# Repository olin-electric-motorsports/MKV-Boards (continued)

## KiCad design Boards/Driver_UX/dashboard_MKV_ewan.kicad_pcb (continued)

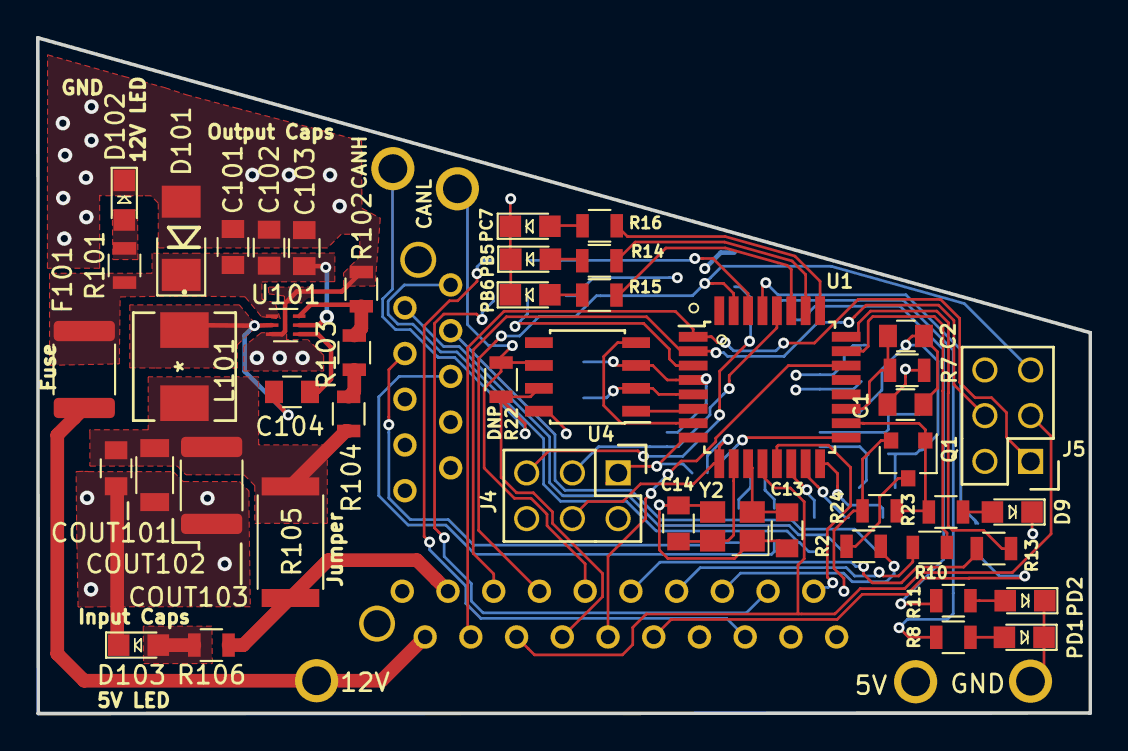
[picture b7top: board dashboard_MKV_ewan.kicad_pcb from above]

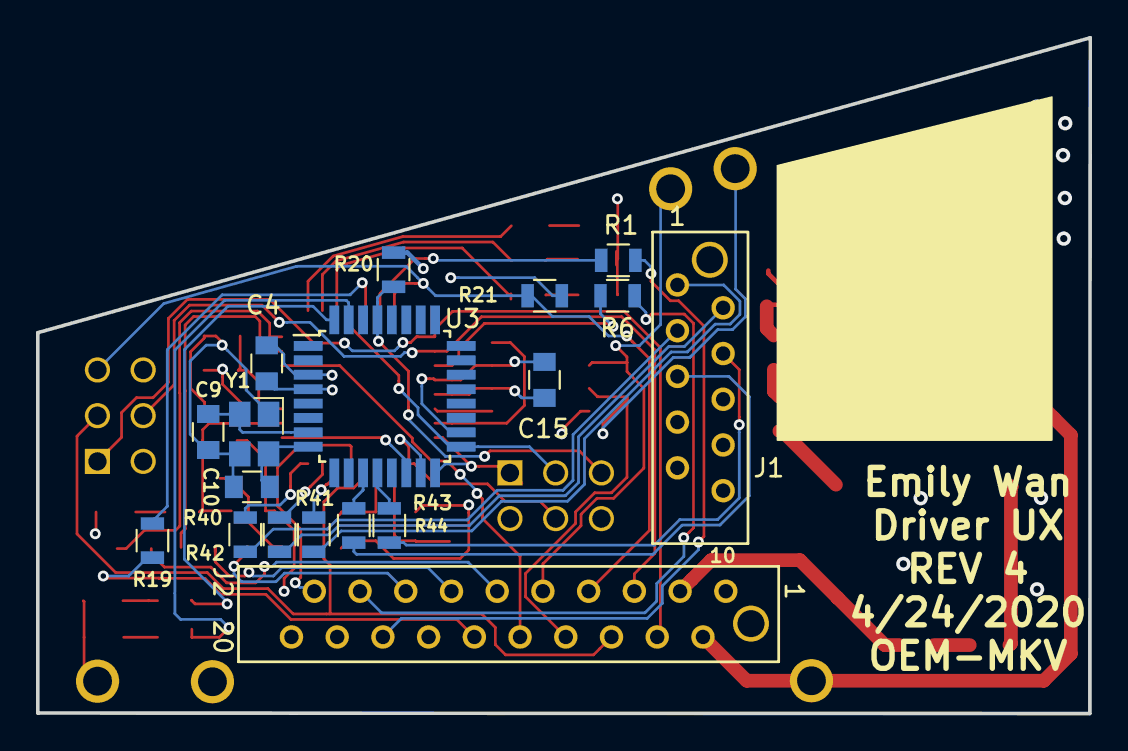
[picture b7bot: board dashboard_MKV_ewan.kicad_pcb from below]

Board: 4 copper layers, 58.5 x 37.5 mm, 70 parts (18 on the bottom side), 65 nets.

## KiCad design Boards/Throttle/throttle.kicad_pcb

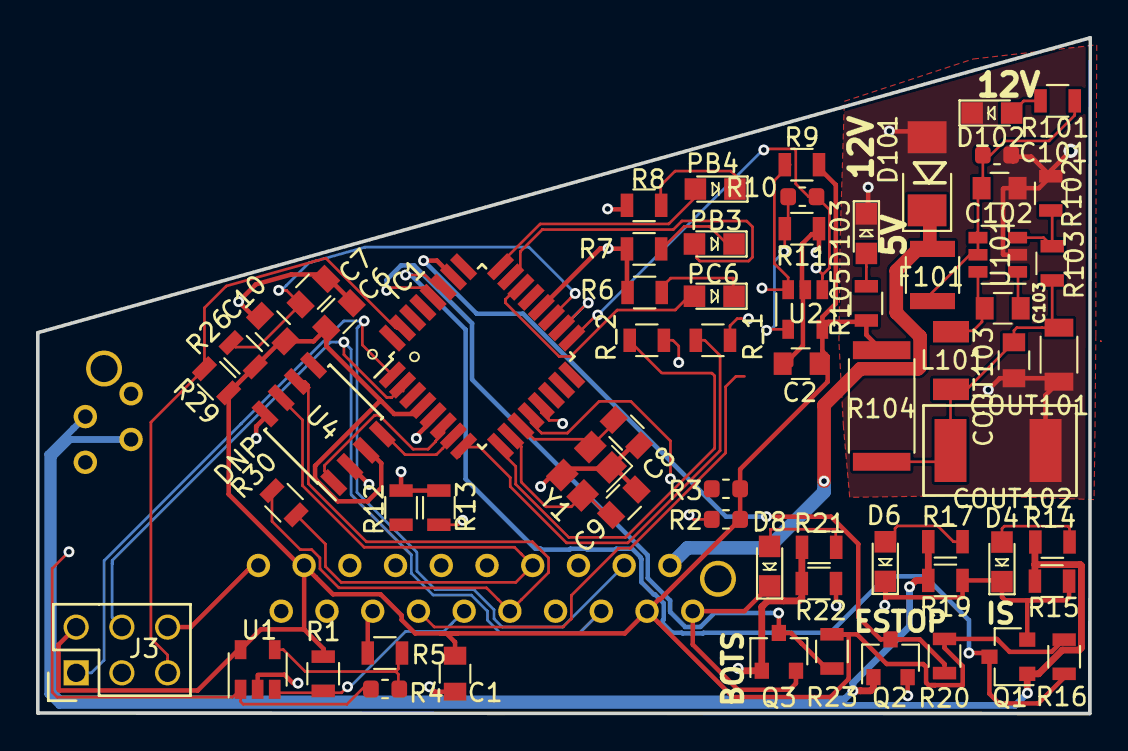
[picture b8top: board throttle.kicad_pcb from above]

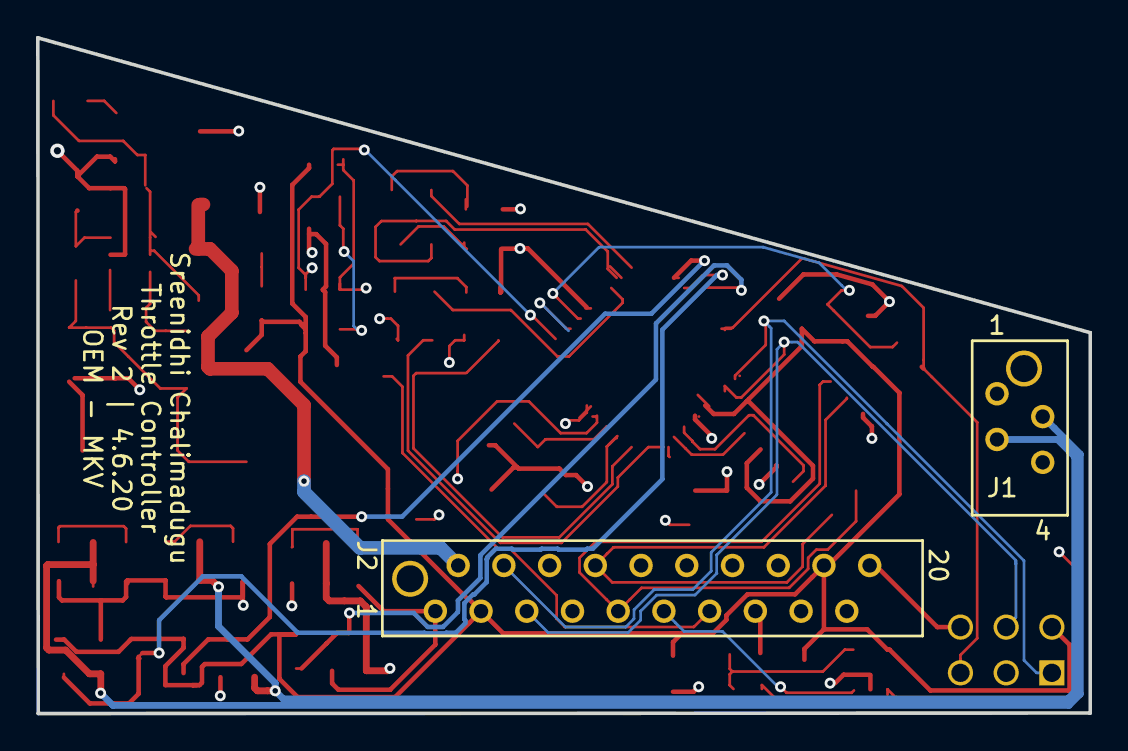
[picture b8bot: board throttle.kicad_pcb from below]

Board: 4 copper layers, 58.5 x 37.5 mm, 68 parts (2 on the bottom side), 49 nets.

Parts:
C1, C2, C6, C10, C103: C_0.1uF; C_0805_OEM
C7: C_100pF; C_0805_OEM
C8, C9: C_30pF; C_0805_OEM
C101: C_0.1uF; C_0603_1608Metric
C102: C_2.2uF; C_0805_OEM
COUT101: C_22uF; C_1206_OEM
COUT102: C_33uF; Fuse_1812
COUT103: C_47uF; C_0805_OEM
D4, D6, D8, D102, D103: LED_0805; LED_0805_OEM
D101: D_Zener_18V; DO-214AA
F101: F_500mA_16V; Fuse_1210
IC1: ATMEGA16M1; TQFP-32_7x7mm_Pitch0.8mm
J1: micromatch_female_TOP_ENTRY_locking_4; micromatch_female_vert_4
J2: micromatch_female_TOP_ENTRY_locking_20; micromatch_female_vert_20
J3: CONN_02X03; Pin_Header_Straight_2x03
L101: L_100uH
PB3, PB4: LED_0805; LED_0805_OEM
PC6: LED_0805; LED_0805_OEM
Q1, Q2, Q3: SSM3K333R; SOT-23F
R1, R9: R_1M; R_0805_OEM
R2, R3: R_0; R_0603_1608Metric
R4, R10: R_0-formula; R_0603_1608Metric
R5, R11: R_2.2k; R_0805_OEM
R6, R7, R8, R101, R105: R_200; R_0805_OEM
R12, R13: R_22K; R_0805_OEM
R14, R17, R21: R_1k; R_0805_OEM
R15, R19, R22: R_100k; R_0805_OEM
R16, R20, R23, R29: R_10k; R_0805_OEM
R26: R_100; R_0805_OEM
R30: R_120 DNP; R_0805_OEM
R102: R_25K; R_0805_OEM
R103: R_100K; R_0805_OEM
R104: R_0_2512; R_2512_OEM
R_1, R_2: R_200; R_0805_OEM
U1, U2: MCP6001; SOT-23-5_OEM
U4: CAN_Transceiver; SOIC-8_3.9x4.9mm_Pitch1.27mm_OEM
U101: TPS560430YF; SOT-23-6_OEM
Y1: Crystal_SMD; Crystal_SMD_FA238

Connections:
+12V: D101.1, F101.2, J2.2
/CANH: J2.8, R30.1, U4.7
/CANL: J2.9, R30.2, U4.6
/DRIVE_MODE_SENSE: IC1.13, J2.19, R13.1
/LED1: J2.16, R_1.1
/LED2: J2.17, R_2.1
/MISO: IC1.1, J2.4, J3.1
/MOSI: IC1.2, J2.5, J3.4
/PROGRAMMINGLED1: IC1.22, PC6.2
/PROGRAMMINGLED2: IC1.23, PB3.2
/PROGRAMMINGLED3: IC1.24, PB4.2
/RESET: IC1.31, J2.7, J3.5, R29.2
/RXCAN: IC1.7, U4.4
/SCK: IC1.12, J2.6, J3.3
/SS_BOTS: J1.1, Q3.1, R21.1, R22.1
/SS_BOTS_OUT: IC1.28, Q3.3, R23.2
/SS_COCKPIT_ESTOP: J1.3, Q2.1, R17.1, R19.1
/SS_ESTOP_OUT: IC1.26, Q2.3, R20.2
/SS_INERTIA_OUT: IC1.27, Q1.3, R16.2
/SS_INERTIA_SWITCH: J1.2, Q1.1, R14.1, R15.1
/THROTTLE1SENSING: IC1.17, R10.1, U2.1
/THROTTLE1_RIGHT_SENSE: J2.11, R1.2, U1.3
/THROTTLE2SENSING: IC1.18, R4.1, U1.1
/THROTTLE2_LEFT_SENSE: J2.14, R9.2, U2.3
/TXCAN: IC1.6, U4.1
GND: C1.1, C2.1, C6.2, C7.2, C8.2, C9.2, C10.2, C101.2, C102.2, COUT101.2, COUT102.2, COUT103.2, D4.1, D6.1, D8.1, D101.2, D102.1, D103.1, IC1.5, IC1.20, J1.4, J2.1, J2.12, J2.15, J2.20, J3.6, Q1.2, Q2.2, Q3.2, R5.2, R6.2, R7.2, R8.2, R11.2, R12.1, R13.2, R15.2, R19.2, R22.2, R102.2, U1.2, U2.2, U4.2, U4.8, U101.2, Y1.2, Y1.4
unnamed: C7.1, IC1.19, R26.2
unnamed: C8.1, IC1.11, Y1.1
unnamed: C9.1, IC1.10, Y1.3
unnamed: C101.1, C102.1, F101.1, R101.1, U101.4, U101.5
unnamed: C103.1, L101.1, U101.6
unnamed: C103.2, U101.1
unnamed: COUT101.1, COUT102.1, COUT103.1, L101.2, R103.1, R104.1
unnamed: PC6.1, R6.1
unnamed: PB3.1, R7.1
unnamed: PB4.1, R8.1
unnamed: D4.2, R14.2
unnamed: D6.2, R17.2
unnamed: D8.2, R21.2
unnamed: D102.2, R101.2
unnamed: D103.2, R105.2
unnamed: IC1.8, R_1.2
unnamed: IC1.9, R_2.2
unnamed: J2.10, R2.1
unnamed: J2.13, R3.2
unnamed: R4.2, R5.1, U1.4
unnamed: R10.2, R11.1, U2.4
unnamed: R102.1, R103.2, U101.3
VCC: C1.2, C2.2, C6.1, C10.1, IC1.4, J2.3, J2.18, J3.2, R1.1, R2.2, R3.1, R9.1, R16.1, R20.1, R23.1, R26.1, R29.1, R104.2, R105.1, U1.5, U2.5, U4.3

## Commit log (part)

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2019-12-02 adding fuses for balancing circuitry
2019-12-02 MegaBoard connectors and dxf
2019-12-02 Finished Schematic with Adi's comments, created V1.0 of Layout
2019-12-03 Debugging board
2019-12-03 Finalize the Suspension Travel Layout
    Move a sensing label to the proper pin on the microcontroller
2019-12-03 BSPD Rev 1 finished
2019-12-03 Generate BSPD/brakelight gerbers
2019-12-03 Reordered shutdown senses on pcb
2019-12-03 Rev. 1
2019-12-03 Finished first(third) pass of schematic
2019-12-03 minor schematic fixes, began layout
2019-12-03 Finish rough draft of schematic
2019-12-03 schematic v2.0 was finally finished
2019-12-03 update template to 1K resistor for 12V led
2019-12-04 fixed bucl resistor mistake
2019-12-04 Add LEDs to shutdown sense board
    Still need to figure out if we need a shutdown sense circuit for Main Fuse
    or if it will come over CAN.
    * Renamed "Brakelight_BSPD" to "BSPD_Brakelight" to stick with naming
    conventions.
2019-12-05 Adds traces to SS board
    No buck convertor or VCC lines in this commit. Still need to
    figure out what is happening with the Main Fuse (i.e. whether
    or not the sense circuit will be on this board or elsewhere).
2019-12-05 Add final traces before importing buck
2019-12-05 laid out components without wires
2019-12-06 Layout V2.0
2019-12-06 Layout V2.5, moved capcaitors closer to chips, eliminates vias in sck, chenaged buck converter positioning after Adi's checkin
2019-12-06 began work on custom bms schematic
2019-12-06 Schematic checked off and PCB Begun
2019-12-06 Complete shutdown sense schematic with buck converter
2019-12-06 Replace 1k with 200k for 5V LEDs
    * Rotate ATmega to be horizontal (allows for fewer route turns)
    * Make LSD driver lines same as VCC (10 mils)
2019-12-10 Edit Schematics
2019-12-10 IMD push
2019-12-10 layout almost complete
2019-12-10 only missing vcc traces now
2019-12-12 Adding First Pass of High Current Buck (3A max)
2019-12-13 Final tweaks
2019-12-13 updates for checkoff
2019-12-13 lcd board with new buck
2019-12-13 Generate BOM and Gerber files
2019-12-13 Final Schamtic and Layout
2019-12-13 Sterring 1st passed layout
2019-12-14 DUX layout Rev1.2
2019-12-15 Charging Cart LCD PCB Layout & Schematic
2019-12-16 Finish schematic
2019-12-16 first pass layout with new buck.
2019-12-17 Beginning changes for laying out board.
2019-12-18 Add draft for lucky to review
2019-12-19 Add small changes
2019-12-20 Add in DXF and start incorporating Lucky's feedback
2019-12-21 Add most revisions besides strain gauge circuits
2019-12-21 Add draft that organizes non-strain gauge circuit parts
2019-12-23 Modify Charging LCD Layout
2019-12-23 Modified buck for throttle board
2019-12-23 Add strain gauge circuits into board cutting boundary
2019-12-23 Improve organization
2019-12-24 Fixed Buck for LCD Screen
2019-12-26 Start wiring strain gauge subcircuits to mux
2019-12-26 Make some improvements to trace organization
2019-12-26 Rotate MUX to optimize its corresponding traces
2019-12-26 Make F.SilkS layer legible
2019-12-28 Minimmize bottom layer traces
2019-12-28 Add logo and name
2019-12-28 Remove vestigial files
2019-12-28 Add gerbers folder and its zip
2019-12-28 added BOM for Chassis_Strain
2019-12-30 deleted extra files
2020-01-02 new edits to layout
2020-01-03 Inital Setup
2020-01-03 Completed LV Interface Rev 1 Things that need to be addressed: - 12V plane is cut off near Ampseal 35 - BSPD CAN Lines are not standard (would be easy to fix on both ends I think) - Could only reason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
    Other changes that were made
    - Significant ampseal changes to accomodate Cooling Board Changes
    - All changes are reflected in Board Interface Sheet
2020-01-03 Saving
2020-01-04 Fixing Charging Cart Dependencies
2020-01-04 Fixed IMD Latch Schematic + Finished Layout
2020-01-04 Fixed VCC & CAN Traces. Added Name Silkscreen
2020-01-04 added new dxf for comparison
2020-01-04 Update micromatch with new pin outs
    Moved TXCAN and RXCAN to positions 3 and 4 to match the LV
    Interface board
2020-01-05 new edits: crystal, retrace
2020-01-05 final lcd screen board
2020-01-05 final final lcd board - added silk screen.
2020-01-05 layout ready for first review
2020-01-06 layout updates (1/5 @20:25)
2020-01-06 layout with graphics
2020-01-06 final layout changes
2020-01-07 gerb files
2020-01-07 pcb commit
2020-01-09 second rev of board
2020-01-11 New DXF stretched out
2020-01-13 fixed footprint error and file cleanup
2020-01-13 acc interface schematic donee
2020-01-15 started internal acc interface
2020-01-15 Save
2020-01-17 Begin Layout
2020-01-17 Revert "Begin Layout"
    This reverts commit f66e97611986f6cb10e89dffa2fa205961dd2a3d.
2020-01-18 Updating AIR Plus Models
2020-01-22 first pass of acc interface and rev1.1 of periph layout
2020-01-23 Edit Layout
2020-01-24 Update BOMs (just to be safe)
2020-01-24 created BOM for board
2020-01-24 BOM for LCD Screen
2020-01-24 rearranged components without traces
2020-01-24 made changes to coding pins, saving before turning other pin
2020-01-24 Necessary tweaks to Charging Cart LCD PCB
2020-01-24 Add BOM
2020-01-25 Air Minus updates 1.24.20 (for Corey)
2020-01-25 Turned pins around and fixed board. Finished Rev 2.
2020-01-25 Turned pins for repositioning. Finished Rev 2
2020-01-26 Board finished, pushing Rev 2
2020-01-26 Adding 3d models of lv Interface, Brakelight, BSPD and Shutdown Boards
2020-01-27 Adding GLVMS to the shutdown circuit
2020-01-27 Layout updated to include GLVMS in Shutdown Circuit
2020-01-27 New connector layouts for air +
2020-01-27 more 3d models
2020-01-28 Fixing Microcmatch 3d models
2020-01-28 Removing Random Text
2020-01-28 HV traces updated
2020-01-28 Rev 3, reduced number of vias and was able to reorganize some tracks
2020-01-29 Controller flipped to back of board
2020-01-30 create bom
2020-01-31 Second Rev PCB
2020-01-31 Fixed labels
2020-02-01 Remove unnecessary files
2020-02-01 Add PDFs of Rev 1 schematics/layouts
2020-02-01 Updating DXF
2020-02-01 shrinking pcb complete
2020-02-01 Minor fixes
2020-02-01 Removed on board cooling Fusing and added additional battery lines
2020-02-02 fixed design rules for via
2020-02-03 added silks to AIR mount plus + gerbs
2020-02-03 made changes to LV BMS board
2020-02-04 Adding cutout notches
2020-02-04 imported new dxf, need to finish drawing sense lines from mm and moving LEDs
2020-02-04 Finished Super Early draft of LV BMS board
2020-02-05 Completed BSPD rev 2
2020-02-05 Addressing review comments ahead of meeting
2020-02-05 Adding Testing Points, Moved Zener Diode (Corrected Orientation)
2020-02-06 Update buck and add test points
    Also remove SCK line from under the ATMega, moved it
    to prevent noise.
2020-02-06 Updated buck on BSPD and added test points
2020-02-07 minor TSAL updates
2020-02-07 Adding lvinterface gerbers
2020-02-07 tons of changes, bug fixes, errors with screw terminals
2020-02-08 Added bypass cap to Logic block; new core layout for ss layout
2020-02-09 modded sch for better routing | layout v1
2020-02-09 new transformer, mounting hole, moved I sensor
2020-02-09 fixed adis suggested changes
2020-02-11 fixed folder problem
2020-02-11 lots of changes to improve naming conventions, consolidate circuitry
2020-02-11 updated final rev 2 with labels and test points
2020-02-12 New BMS core DXF, proper GLV HV spacing
2020-02-13 Final, and slight, changes to layout
2020-02-13 BMS core rev1.0 for shipment
2020-02-13 Updating Gates Names
2020-02-14 added in resistor values
2020-02-14 added mounting holes
2020-02-14 started changes to TSAL schematic
2020-02-15 documented a ton of junk
2020-02-19 completed initial design review fixes. more to come
2020-02-21 design review changes
2020-02-21 IMD Latch Fix Rev 2
2020-02-21 LV Interface Updates
2020-02-25 Fixed 12V in schematic
2020-02-25 fixed drc issues
2020-02-26 TSAL First Pass
2020-02-27 start of new layout
2020-02-27 AIR Minus Rev 2 - No Fuse
2020-02-27 AIR mount changes
2020-02-27 First draft of BMS Periph V2
2020-02-29 Updating AIR Mount Boards
2020-02-29 minor changes
2020-02-29 IMD Latch changes
2020-03-02 Imported new DXF, uploading Rev 5
2020-03-02 Fixed shape of BSPD board
2020-03-02 Update board shape for Shutdown Sense
2020-03-03 Changed labels for diodes
2020-03-03 IMD latch Rev 2 Updates 3.2.2020
2020-03-03 uploading current board so you can revise
2020-03-03 New Board Shape for DUX
2020-03-04 test points and silkscreen
2020-03-04 added in adi's footprint
2020-03-05 Add pdf and step file
2020-03-05 Rename rename Chassis_Strain to Suspension_Strain
2020-03-05 new Throttle board shape
2020-03-05 schematic and layout fixes
2020-03-06 SS Boards Rev 2
2020-03-06 Revised version of Rev 5 with final edge cuts
2020-03-06 Fixing Layout to Account for Schematic Changes
2020-03-06 Adding 9V LED Trace
2020-03-06 Final SS Boards Rev 2
2020-03-06 failed layout v0
2020-03-08 draft of rev 2 done
2020-03-08 Edit schematics and layout
2020-03-08 Generated new STEP files and GERBs
2020-03-09 fixed connector overlap issues & minor pinout changes
2020-03-09 adding buck
2020-03-10 Updated BSPD/Brakelight with Manu's fixes
2020-03-10 Updated Shutdown Sense with Manu's fixes
2020-03-10 Updating Dux Interface Cad models
2020-03-10 More DUX updates
2020-03-11 Fixed mechanical interference
2020-03-11 Adding DUX step
2020-03-14 Updated BSPD/Brakelight with Adi's changes
    Also deleted old files from rev 1 and renamed files to keep with naming
    convention
2020-03-14 Deleted unnecessary files from rev 1
2020-04-05 3 rev of dashboard layout
2020-04-07 rev 2 done
2020-04-12 some partial layout changes
2020-04-12 fixed general spacing issues, bypass capacitor spacing, CAN Tranciever spacing / vias & crystal spacing / vias
2020-04-15 updated example1 with key
2020-04-19 almost all layout fixes except footprint screw terminal footprint
2020-04-25 finished rev4, ready for feedback
2020-04-28 Add Troubleshooting board folder
2020-05-03 Added 3A Buck Variant
2020-05-03 Included documentation on final schematic and layout
2020-05-03 added in screw terminal footprint to layout
2020-05-03 Added rectangular silk screen to back of PCB
2020-05-12 added some debug LEDs
2020-05-24 export schematics to pdf
2020-07-16 Rev 3 of Air Mounts
2020-11-04 basically just coping the template
2021-04-06 changes to lv bms
2021-05-18 project files for service section controller
2021-05-18 boilerplate for service section schematics
2021-05-18 added ss carryover boards
2021-05-18 carried over relevant service section circuitry
2021-05-18 adding table of contents for sensing board
2021-05-18 Add wheel_speed_carryover
2021-05-18 Add suspension strain carryover
2021-05-18 Add suspension_strain_carryover
2021-05-18 Fix components in sensing_strain_carryover
2021-05-18 Add micro.sch with added components.
2021-05-18 Work on micros.sch
2021-05-19 Remove generated and useless files
    NOTE: If you see something that shouldn't have been deleted, let someone
    know. All gerbers, netlists, BoMs, images, and pdfs have been removed.
    Also, all backup files and most cache files.
2021-05-22 changed labels to global and added lin reg
2021-05-22 Started working on connectors and fixed tsal lin reg part
2021-05-23 suspension strain start-- need to do more work to validate values for passives
2021-05-23 Add datasheet to LDO.
2021-05-27 repin shutdown circuit + general schematic cleanup
2021-05-28 modify net labels for LSD circuits
2021-05-28 eliminate nonsense net labels on tsal schematic
2021-05-31 changed labels and power nets and added fusing
    changed relevant labels to global labels and checked that the
    naming is correct. Changed vcc nets to corresponding 5v or 12v.
2021-06-19 added .pdf for rev1 lv_bms_2
2021-07-22 Changed micro board to be less cramped, and added global labels.
2021-07-22 Make power schematic less cramped & make 3.3V global net
2021-07-22 Moved indicator LED & resistor before 0 ohm resistor
2021-07-22 Copy over wheel speed carryover schematic.
2021-07-28 Change vcc to +5V and fix net labels.
2021-07-28 Change VCC to +5V.
2021-08-01 Delete power.sch
    for merge conflict resolution
2021-08-01 Fix disconnected net, change VCC to +5V power symbol, and change 3.3V to global net
2021-09-08 Fix net labels, clean schematic.
2021-09-10 Fixed net labels and add missing components.
    Changed power flags to global net labels, connected strain gauge nets to ATMEGA16M1, added LEDs where needed, and changed net labels to connect as needed.
2021-09-10 Add space between net labels and block.
2021-09-14 moved all circuitry to 50mil grid, fixed net labels, fixed footprints, added connectors
2021-09-14 rescue lib removed
2021-09-15 updated schematic
2021-09-15 removed all traces and planes from layout. started adding test points
2021-09-27 Updating LVInterface Layout - Moving Pull up resistors for GLV current gauge
